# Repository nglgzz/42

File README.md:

# 42 Keyboard

A mechanical keyboard with 42 keys.

## Features

- 40% – Each key is at most one unit of distance from where the finger that
  should press it rests. In other words there's no awkward reaching for keys
  that are placed far from the home row.
- Staggered columns - Because a comfortable keyboard should follow the shape of
  your hands.
- Low profile - The PCB supports Choc (PG1350) switch mounts as well as Cherry MX/Alps.

## Pics

- Finished keyboard
  <br/>
  <br/>
- PCB
  <br/>

## Project Structure

- [Build](./build/README.md) – Build log, bill of materials, tips on where to
  source parts, assembling tips, learning resources I used while designing this
  keyboard.

- [Case](./case/README.md) – Fusion 360 project and STL files for 3D printing
  the enclosure.

- [Firmware](./firmware/README.md) – QMK configuration. There is a Makefile to
  build and load the firmware.

- [PCB](./pcb/README.md) – Kicad project and Gerber files for manufacturing the
  circuit board.

## Why?

In January 2018 I wanted a keyboard with a specific set of features. The
simplest options to get that keyboard were to wait for a group-buy or build my
own. Waiting time and costs for both options seemed similar, so I went with the
option where I would learn the most.

Needs and knowledge changed over time, so I made different iterations to add new
features and account for the lessons learned from previous builds.

## Feedback

If you have some feedback or questions, feel free to [create an issue](https://github.com/nglgzz/42/issues/new). Your input is more than welcome!

## Previous Versions

- [version 3.1](https://github.com/nglgzz/42/tree/rev-3.1) –
  custom PCB, QMK firmware, USB C, Elite-C v4
  <br/>
- [version 3](https://github.com/nglgzz/42/tree/rev-3) –
  custom PCB, QMK firmware, Bluetooth, micro USB, Adafruit Feather 32u4 Bluefruit LE
  <br/>
- [version 2](https://github.com/nglgzz/42/tree/rev-2) –
  handwired, QMK firmware, Bluetooth, micro USB, Adafruit Feather 32u4 Bluefruit LE
  <br/>
- [version 1:](https://github.com/nglgzz/42/tree/rev-1)
  custom PCB, Split, TMK firmware, USB C, Teensy 2.0
  <br/>

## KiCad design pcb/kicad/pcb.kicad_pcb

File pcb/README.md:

# [42 Keyboard](../README.md) – PCB

Here you can find the Kicad project for the keyboard's circuit board, and the Gerber files needed to manufacture it.

## Useful Resources

[../build/resources.md](../build/resources.md#pcb)

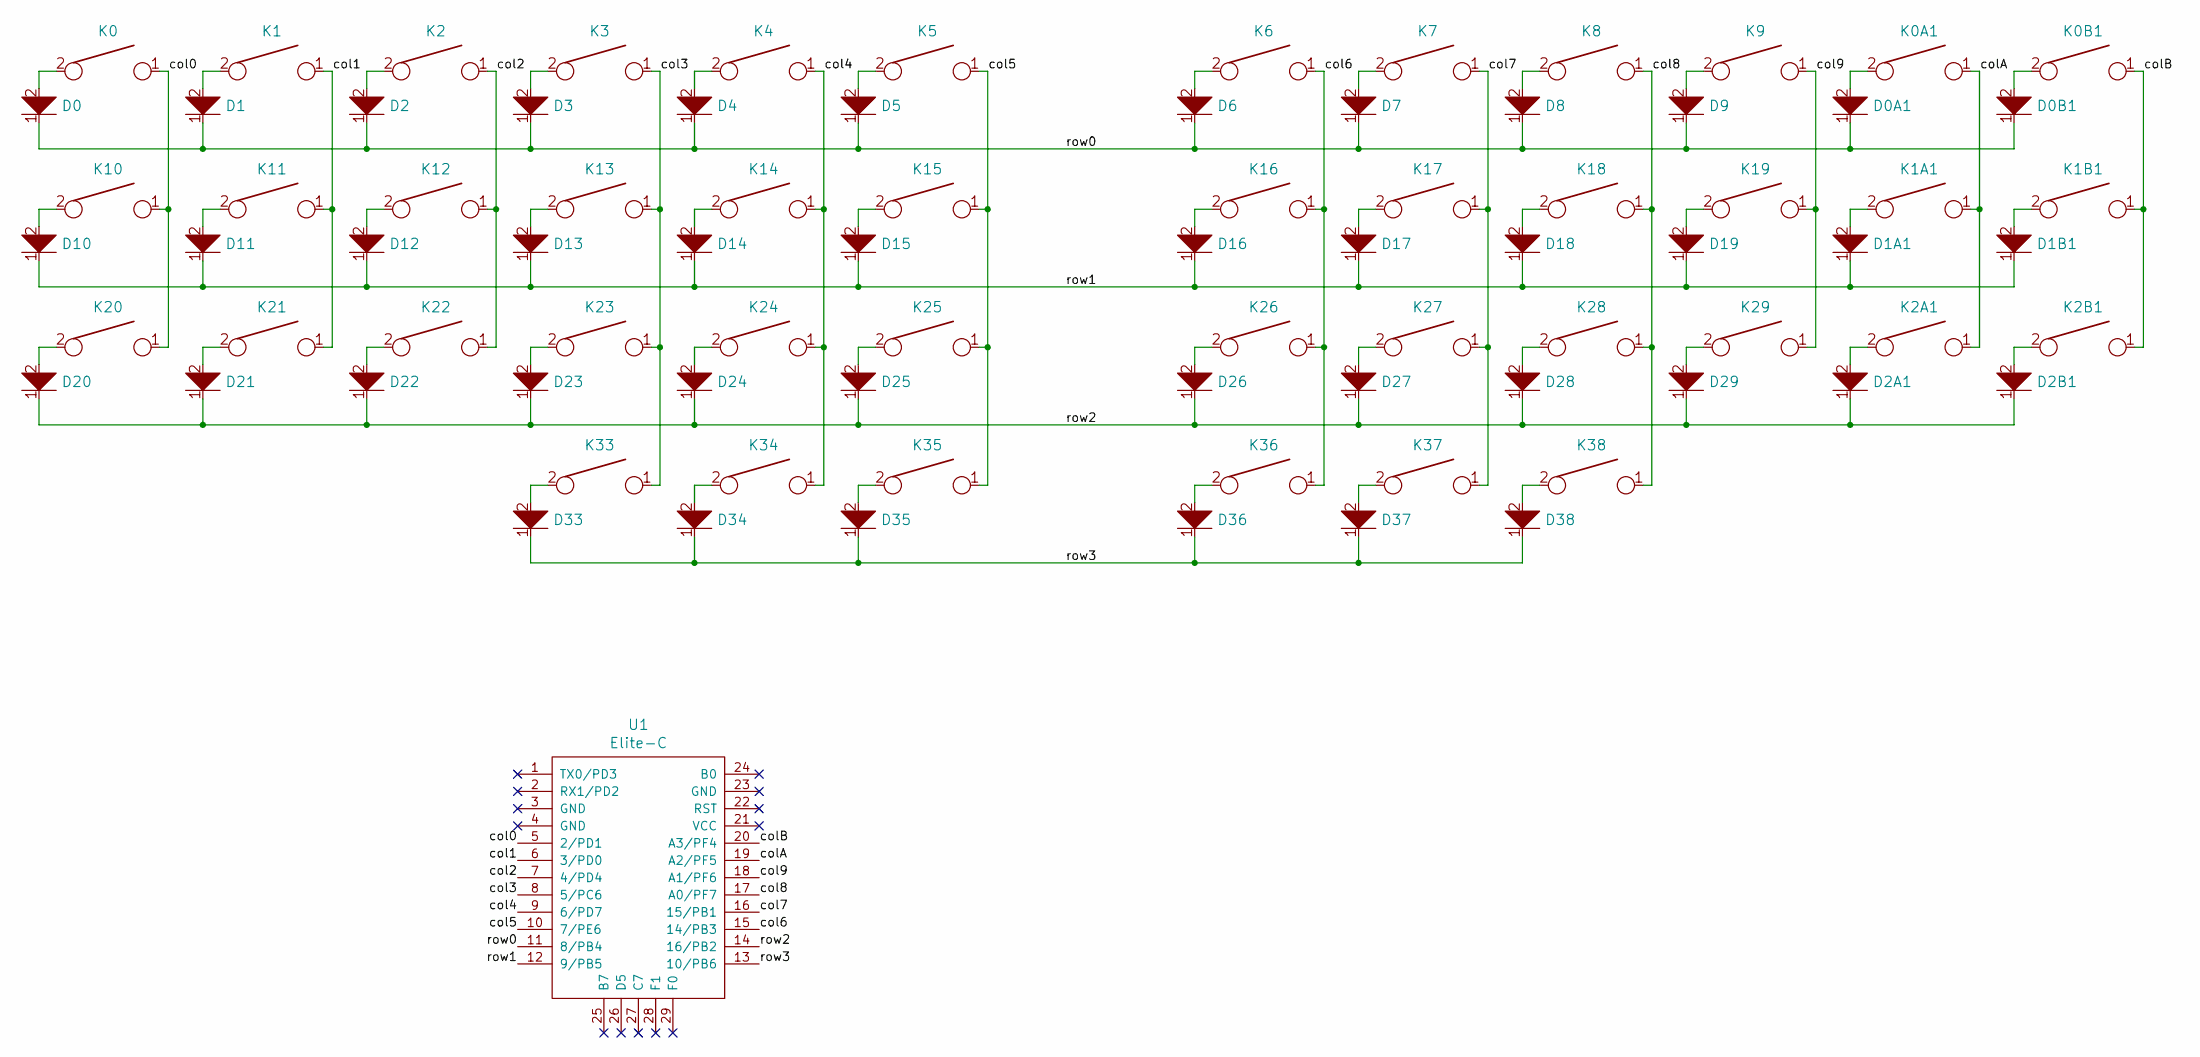
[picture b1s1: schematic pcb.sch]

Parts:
D0, D0A1, D0B1, D1, D1A1, D1B1, D2, D2A1, D2B1, D3, D4, D5, D6, D7, D8, D9, D10, D11, D12, D13, D14, D15, D16, D17, D18, D19, D20, D21, D22, D23, D24, D25, D26, D27, D28, D29, D33, D34, D35, D36, D37, D38: D; D_SOD123_axial
K0, K0A1, K0B1, K1, K1A1, K1B1, K2, K2A1, K2B1, K3, K4, K5, K6, K7, K8, K9, K10, K11, K12, K13, K14, K15, K16, K17, K18, K19, K20, K21, K22, K23, K24, K25, K26, K27, K28, K29, K33, K34, K35, K36, K37, K38: KEYSW; MX-Alps-Choc-1U-NoLED
U1: Elite-C; Elite-C-castellated-29pin-holes

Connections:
/col0: K0.1, K10.1, K20.1, U1.5 (2/PD1)
/col1: K1.1, K11.1, K21.1, U1.6 (3/PD0)
/col2: K2.1, K12.1, K22.1, U1.7 (4/PD4)
/col3: K3.1, K13.1, K23.1, K33.1, U1.8 (5/PC6)
/col4: K4.1, K14.1, K24.1, K34.1, U1.9 (6/PD7)
/col5: K5.1, K15.1, K25.1, K35.1, U1.10 (7/PE6)
/col6: K6.1, K16.1, K26.1, K36.1, U1.15 (14/PB3)
/col7: K7.1, K17.1, K27.1, K37.1, U1.16 (15/PB1)
/col8: K8.1, K18.1, K28.1, K38.1, U1.17 (A0/PF7)
/col9: K9.1, K19.1, K29.1, U1.18 (A1/PF6)
/colA: K0A1.1, K1A1.1, K2A1.1, U1.19 (A2/PF5)
/colB: K0B1.1, K1B1.1, K2B1.1, U1.20 (A3/PF4)
/row0: D0.1, D0A1.1, D0B1.1, D1.1, D2.1, D3.1, D4.1, D5.1, D6.1, D7.1, D8.1, D9.1, U1.11 (8/PB4)
/row1: D1A1.1, D1B1.1, D10.1, D11.1, D12.1, D13.1, D14.1, D15.1, D16.1, D17.1, D18.1, D19.1, U1.12 (9/PB5)
/row2: D2A1.1, D2B1.1, D20.1, D21.1, D22.1, D23.1, D24.1, D25.1, D26.1, D27.1, D28.1, D29.1, U1.14 (16/PB2)
/row3: D33.1, D34.1, D35.1, D36.1, D37.1, D38.1, U1.13 (10/PB6)
unnamed: D0.2, K0.2
unnamed: D0A1.2, K0A1.2
unnamed: D0B1.2, K0B1.2
unnamed: D1.2, K1.2
unnamed: D1A1.2, K1A1.2
unnamed: D1B1.2, K1B1.2
unnamed: D2.2, K2.2
unnamed: D2A1.2, K2A1.2
unnamed: D2B1.2, K2B1.2
unnamed: D3.2, K3.2
unnamed: D4.2, K4.2
unnamed: D5.2, K5.2
unnamed: D6.2, K6.2
unnamed: D7.2, K7.2
unnamed: D8.2, K8.2
unnamed: D9.2, K9.2
unnamed: D10.2, K10.2
unnamed: D11.2, K11.2
unnamed: D12.2, K12.2
unnamed: D13.2, K13.2
unnamed: D14.2, K14.2
unnamed: D15.2, K15.2
unnamed: D16.2, K16.2
unnamed: D17.2, K17.2
unnamed: D18.2, K18.2
unnamed: D19.2, K19.2
unnamed: D20.2, K20.2
unnamed: D21.2, K21.2
unnamed: D22.2, K22.2
unnamed: D23.2, K23.2
unnamed: D24.2, K24.2
unnamed: D25.2, K25.2
unnamed: D26.2, K26.2
unnamed: D27.2, K27.2
unnamed: D28.2, K28.2
unnamed: D29.2, K29.2
unnamed: D33.2, K33.2
unnamed: D34.2, K34.2
unnamed: D35.2, K35.2
unnamed: D36.2, K36.2
unnamed: D37.2, K37.2
unnamed: D38.2, K38.2

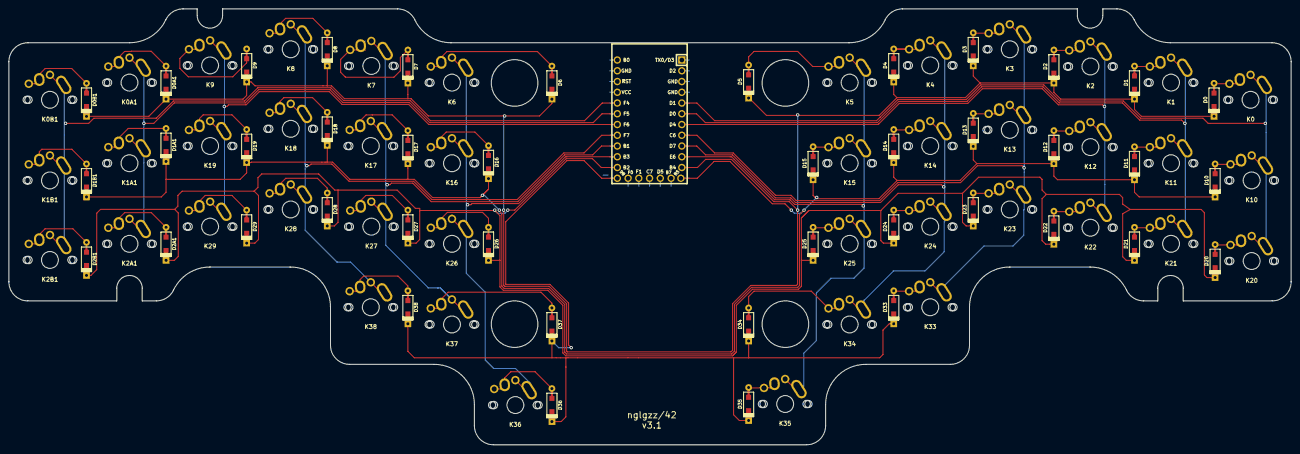
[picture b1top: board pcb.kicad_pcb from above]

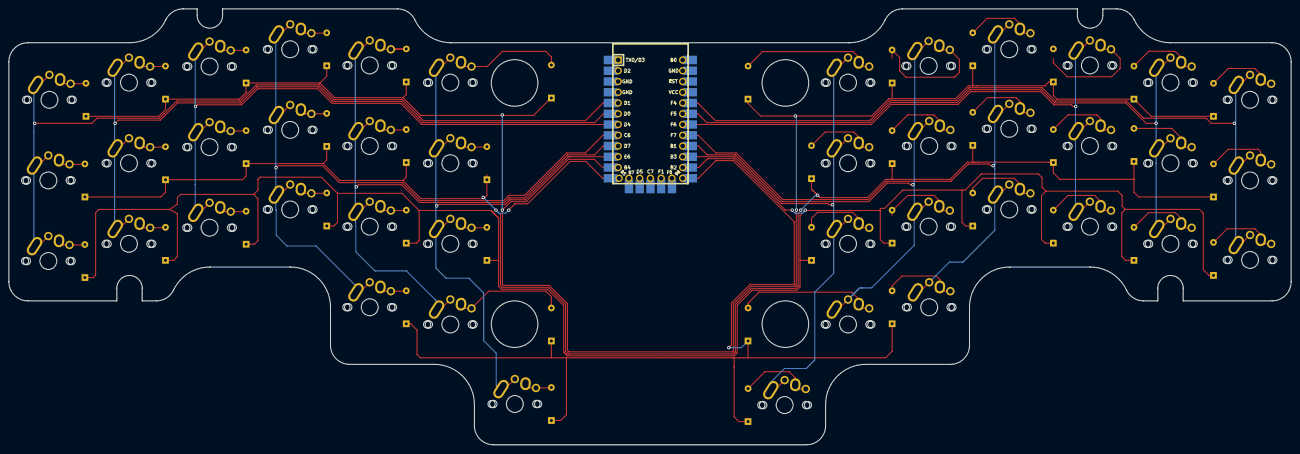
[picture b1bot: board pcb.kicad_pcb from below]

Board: 2 copper layers, 303.0 x 103.0 mm, 85 parts (43 on the bottom side), 58 nets.

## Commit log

2018-03-11 added case and gerber files
2018-03-11 added kicad project
2018-03-11 added firmware
2018-03-11 rounded case corners
2018-03-11 added readmes
2018-03-11 changed formatting
2018-03-13 fixed position of thumb key footprint
2018-03-13 ignore firmware binaries
2018-03-13 removed controller and usb receptacle holes from right side
2018-03-14 fixed inverted connections on USB receptacle
2018-03-14 added resources fixed modifiers on firmware
2018-03-14 caps is useless
2018-03-22 added license
2018-03-22 added todo
2018-03-26 rounded corners, ignore backup saves
2018-03-26 ignore backup saves
2018-03-26 moved receptacles to the back side, rewired connections
2018-03-29 updated gerber files
2018-04-24 added image of keyboard
2018-04-26 this line gave me hours of anxiety, but now it's all over
2018-05-03 updated layout
2018-05-12 update thumb keys functions
2018-05-15 add mouse layer
2018-05-15 add caps
2018-05-15 fix mouse layer
2018-05-15 add i3 help binding
2018-05-20 update case
2018-06-02 update case files, add gaming mode
2019-02-03 Add v2 files
2019-02-05 Keymap: move definitions, add mouse/music layer
2019-04-02 Keymap: add gaming layer
2019-05-13 Case: model version 3
2019-06-06 PCB: add kicad and gerber files
2019-06-08 PCB: add hole for battery cables
2019-06-18 Gitignore: update gitignore
2019-06-18 Readme: update images for v3
2019-06-20 Case: update STL files
2019-06-20 Case: update readme
2020-04-11 Firmware: remove old files and link to QMK repo
2020-04-11 Readme: add modeling resource
2020-04-11 Keymap: remove gaming layer
2020-04-11 PCB: add v4 circuit board
    - Split layout with Proton C and MCP 23017
    - Sides can be connected with spring loaded pins or TRRS connectors
2020-04-11 Firmware: add v4 files
    Define a custom matrix for using the Proton C with the MCP 23017
    IO expander.
2020-04-11 PCB: fix TRRS connectors position
2020-04-11 Add more resources
2020-04-11 PCB: update gerber files
2020-04-11 PCB: fix wiring of TRRS connectors
2020-04-11 PCB: increase size of resistor footprints
2020-04-11 PCB: Fix position of female pin connector
2020-04-11 PCB: generate gerber files
2020-04-11 Update LICENSE
2020-04-12 Update documentation
2020-04-13 Case: add fusion 360 project
2020-04-15 Firmware: initialize expander on matrix scan
    Also adds a visual cue to show when both sides
    are connected.
    Closes #1.
2020-04-25 Update materials list
2020-05-23 Update layout
2021-01-06 Move different revisions in different branches
2021-10-17 Add Elite C pinout
2021-10-17 Redesign PCB for Elite-C
2021-10-17 Add support for Choc v1 switches
2021-10-21 Add PCB support for Pro Micro
2021-10-21 Update QMK, configure new pins for columns and rows
2021-10-21 Add note about v4 not working
2021-10-21 Cleanup readmes
2021-10-24 Update firmware makefile, remove QMK git module
2021-10-24 Update gerber files
2022-01-17 Add STL files for case
2022-01-17 Update pics
2023-02-28 Add test zmk configuration
2023-03-12 Fix zmk configuration
2024-01-31 Update firmware
2026-04-04 Update case files and description
2026-04-04 Update keymap
2026-04-21 Update case front fillet and connector recess
2026-06-04 Switch to liatris board
